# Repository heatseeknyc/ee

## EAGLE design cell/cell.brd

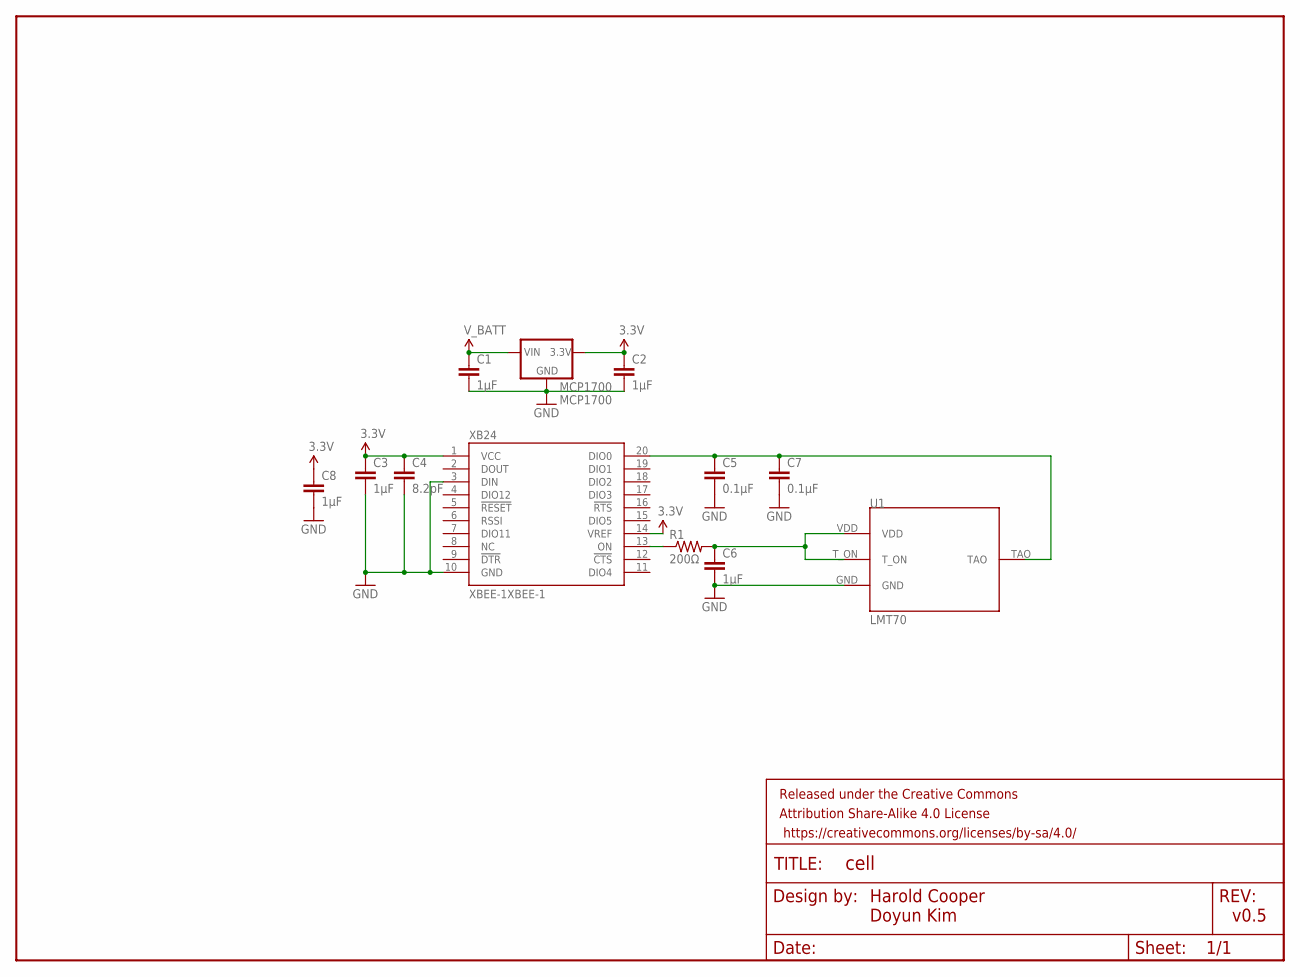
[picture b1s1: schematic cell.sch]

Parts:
C1, C2, C3, C6, C8: 1µF; 0805
C4: 8.2pF; 0805
C5, C7: 0.1µF; 0805
FRAME1: FRAME-LETTER; CREATIVE_COMMONS
MCP1700: MCP1700; SOT-89-3
R1: 200Ω; 0805
U1: LMT70; YFP0004
XB24: XBEE-1XBEE-1; XBEE-1

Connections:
3.3V: C2.1, C3.1, C4.1, C8.1, MCP1700.3 (3.3V), XB24.1 (VCC), XB24.14 (VREF)
GND: C1.2, C2.2, C3.2, C4.2, C5.2, C6.2, C7.2, C8.2, MCP1700.1 (GND), U1.GND, XB24.3 (DIN), XB24.10 (GND)
unnamed: C6.1, R1.2, U1.T_ON, U1.VDD
unnamed: R1.1, XB24.13 (ON)
unnamed: C5.1, C7.1, U1.TAO, XB24.20 (DIO0)
V_BATT: C1.1, MCP1700.2 (IN)

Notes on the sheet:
Harold Cooper Doyun Kim
v0.5

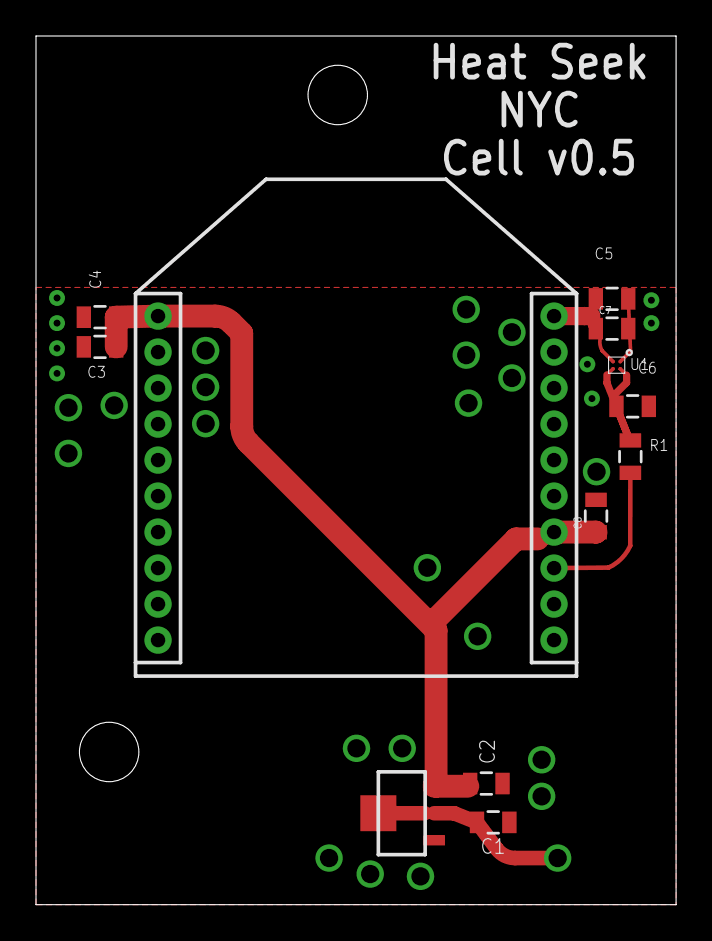
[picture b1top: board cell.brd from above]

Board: 2 copper layers, 35.6 x 48.3 mm, 13 parts (0 on the bottom side), 6 nets.

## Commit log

2015-12-04 Doodles from @raphaelabrams - simplified the power supply rail to a star - strengthened the ground plane - added several decoupling capacitors

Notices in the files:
parts and their libraries:
SparkFun-Aesthetics: Licensing: Creative Commons ShareAlike 4.0 International - https://creativecommons.org/licenses/by-sa/4.0
SparkFun-Aesthetics: Released under the Creative Commons Attribution Share-Alike 4.0 License
SparkFun-Aesthetics: https://creativecommons.org/licenses/by-sa/4.0
